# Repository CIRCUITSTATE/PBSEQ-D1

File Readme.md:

# PBSEQ-D1

**PBSEQ-D1** is a push-button based power sequencer demo board designed in KiCad. You can press the push-button momentarily to turn on the output. Pressing and and holding will turn off the output. A PMOS transistor is used as a high-side switch to control the power. An NMOS transistor controls the power sequencing. This demo project is fully open-source and you can find the source design files here.

A tutorial of designing and testing the circuit will soon be available at [CIRCUITSTATE](https://www.circuitstate.com/).

## Project Details

- **Parent Project:** PBSEQ
- **Variant Name:** PBSEQ-D1
- **Latest Revision:** `R0.2`
- **EDA Tools:** KiCad V8
- **Layer Count:** 2
- **Board Thickness:** 1.6 mm
- **Dimensions:** 19 x 19 mm

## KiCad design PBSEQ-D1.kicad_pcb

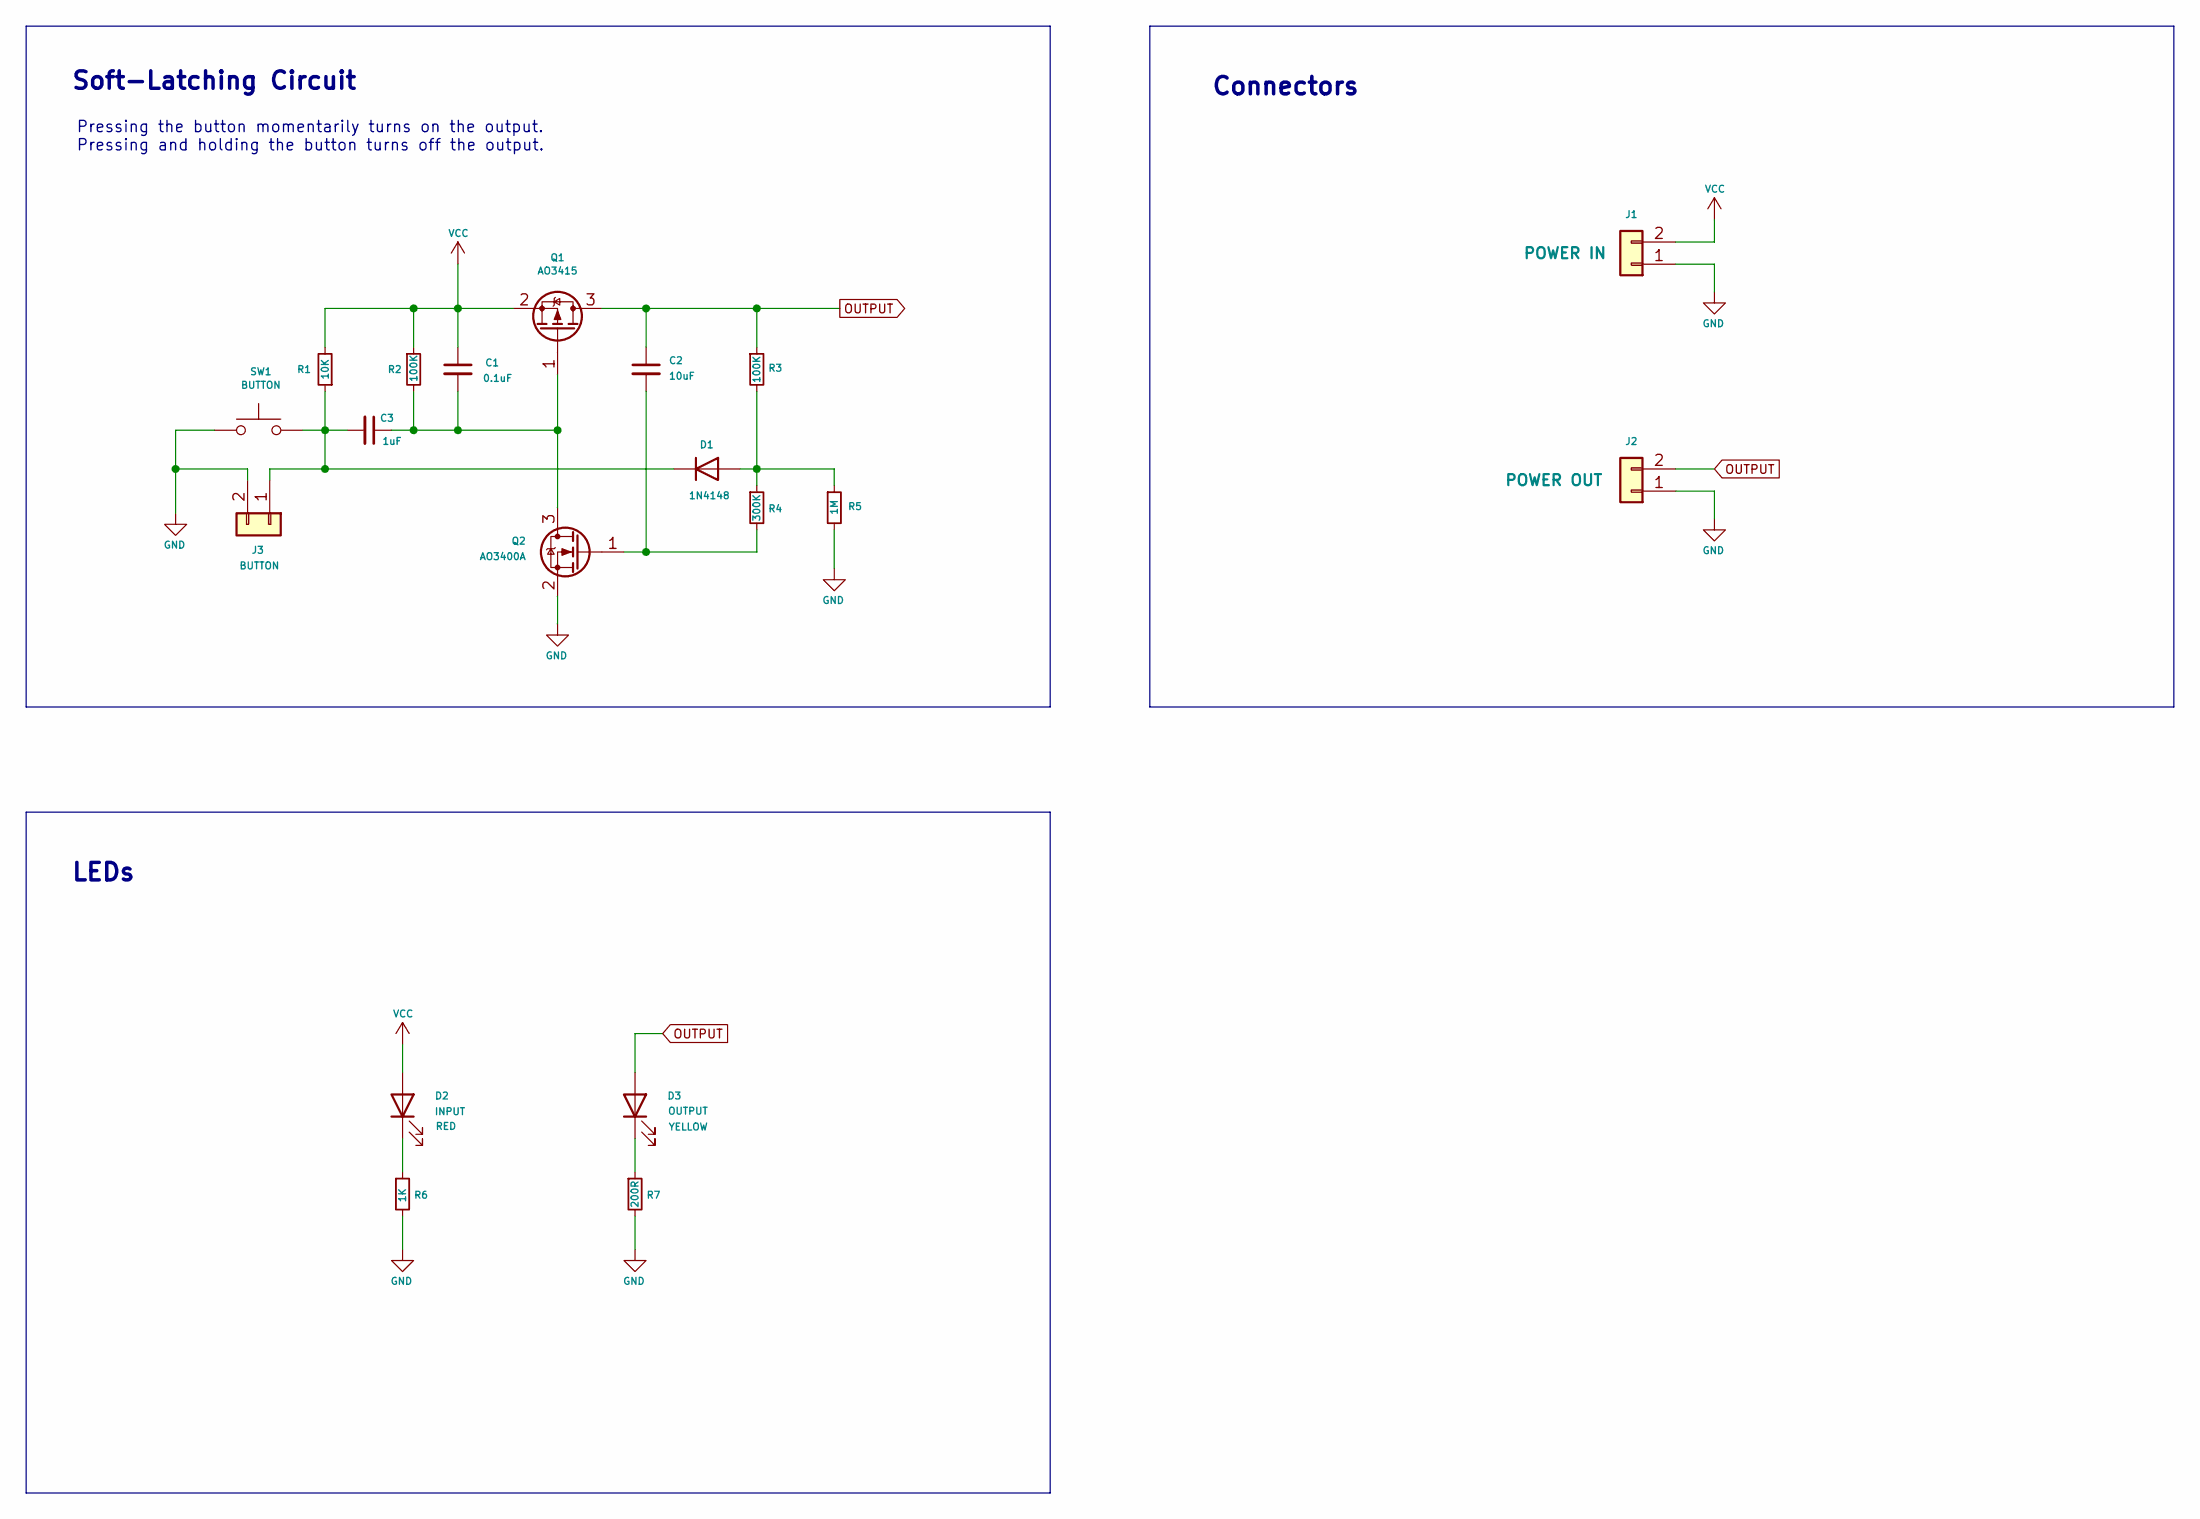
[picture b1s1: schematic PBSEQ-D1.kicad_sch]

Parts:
C1: 0.1uF; C_0603_1608Metric_Pad1.08x0.95mm_HandSolder; MPN 0603B104J500CT
C2: 10uF; C_0603_1608Metric_Pad1.08x0.95mm_HandSolder; MPN 0603X106K100CT
C3: 1uF; C_0603_1608Metric_Pad1.08x0.95mm_HandSolder; MPN CC0603KRX5R9BB105
D1: 1N4148; D_SOD-323_HandSoldering; MPN 1N4148WS
D2: RED; LED_0603_1608Metric_Pad1.05x0.95mm_HandSolder; MPN 19-21SURC/S530-A2/TR8
D3: YELLOW; LED_0603_1608Metric_Pad1.05x0.95mm_HandSolder; MPN 19-213/Y2C-FN2P2VZ/3T
J1: POWER IN; PinHeader_1x02_P2.54mm_Vertical; MPN DNP
J2: POWER OUT; PinHeader_1x02_P2.54mm_Vertical; MPN DNP
J3: BUTTON; PinHeader_1x02_P2.54mm_Vertical; MPN DNP
Q1: AO3415; SOT-23; MPN AO3415
Q2: AO3400A; SOT-23; MPN AO3400A
R1: 10K; R_0603_1608Metric_Pad0.98x0.95mm_HandSolder; MPN WR06X1002FTL
R2, R3: 100K; R_0603_1608Metric_Pad0.98x0.95mm_HandSolder; MPN WR06X1003FTL
R4: 300K; R_0603_1608Metric_Pad0.98x0.95mm_HandSolder; MPN WR06X3003FTL
R5: 1M; R_0603_1608Metric_Pad0.98x0.95mm_HandSolder; MPN WR06X1004FTL
R6: 1K; R_0603_1608Metric_Pad0.98x0.95mm_HandSolder; MPN WR06X1001FTL
R7: 200R; R_0603_1608Metric_Pad0.98x0.95mm_HandSolder; MPN WR06X2000FTL
SW1: BUTTON; CK_SW_SPST_UK-B0273-SP25Y; MPN TS-1088R-02526

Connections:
GND: J1.1, J2.1, J3.2, Q2.2 (S), R5.2, R6.2, R7.2, SW1.1
unnamed: D1.2 (A), R3.2, R4.1, R5.1
unnamed: C3.2, D1.1 (K), J3.1, R1.1, SW1.2
unnamed: D2.1 (K), R6.1
unnamed: D3.1 (K), R7.1
unnamed: C1.2, C3.1, Q1.1 (G), Q2.3 (D), R2.2
unnamed: C2.2, Q2.1 (G), R4.2
OUTPUT: C2.1, D3.2 (A), J2.2, Q1.3 (D), R3.1
VCC: C1.1, D2.2 (A), J1.2, Q1.2 (S), R1.2, R2.1

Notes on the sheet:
Connectors
LEDs
Pressing the button momentarily turns on the output. Pressing and holding the button turns off the output.
Soft-Latching Circuit

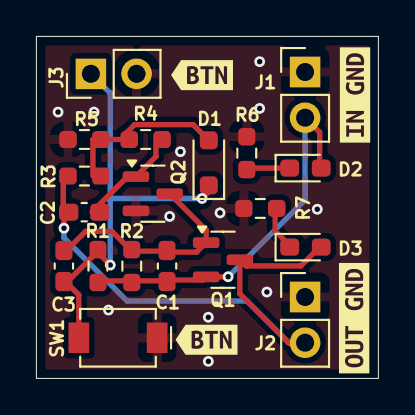
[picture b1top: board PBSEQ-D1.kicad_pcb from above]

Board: 2 copper layers, 19.0 x 19.0 mm, 24 parts (1 on the bottom side), 9 nets.

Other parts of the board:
kibuzzard-663FBC0C, kibuzzard-663FBC0C#2: G***; kibuzzard-663FBC0C
kibuzzard-663FBCF2: G***; kibuzzard-663FBCF2
kibuzzard-663FBD0F: G***; kibuzzard-663FBD0F
kibuzzard-665C27BB: G***; kibuzzard-665C27BB

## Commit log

2024-05-12 R0.1 Init Commit
    * Completed PCB routing.
    * DRC passes.
    * Exported manufacturing files.
    * New Revision `R0.1`.
2024-05-12 Added gitignore
2024-05-17 Exported images of the PCB
    * Added XLS BoM.
    * Updated Readme.
2024-05-17 Udpated Readme
2024-06-02 R0.2
    * Fixed the diode connection issue. The Cathode was connected to the wrong point.
    * Updated `Q1` to AO3415.
    * The circuit has been tested and working.
    * Updated all 0603 footprints to hand-soldering type for easy soldering.
    * Rearranged the silkscreen labels.
    * DRC passes.
